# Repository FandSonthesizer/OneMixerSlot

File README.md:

# OneMixerSlot

This is one strip of the modular mixer, it can do voltage controlled panning in the stereo field.

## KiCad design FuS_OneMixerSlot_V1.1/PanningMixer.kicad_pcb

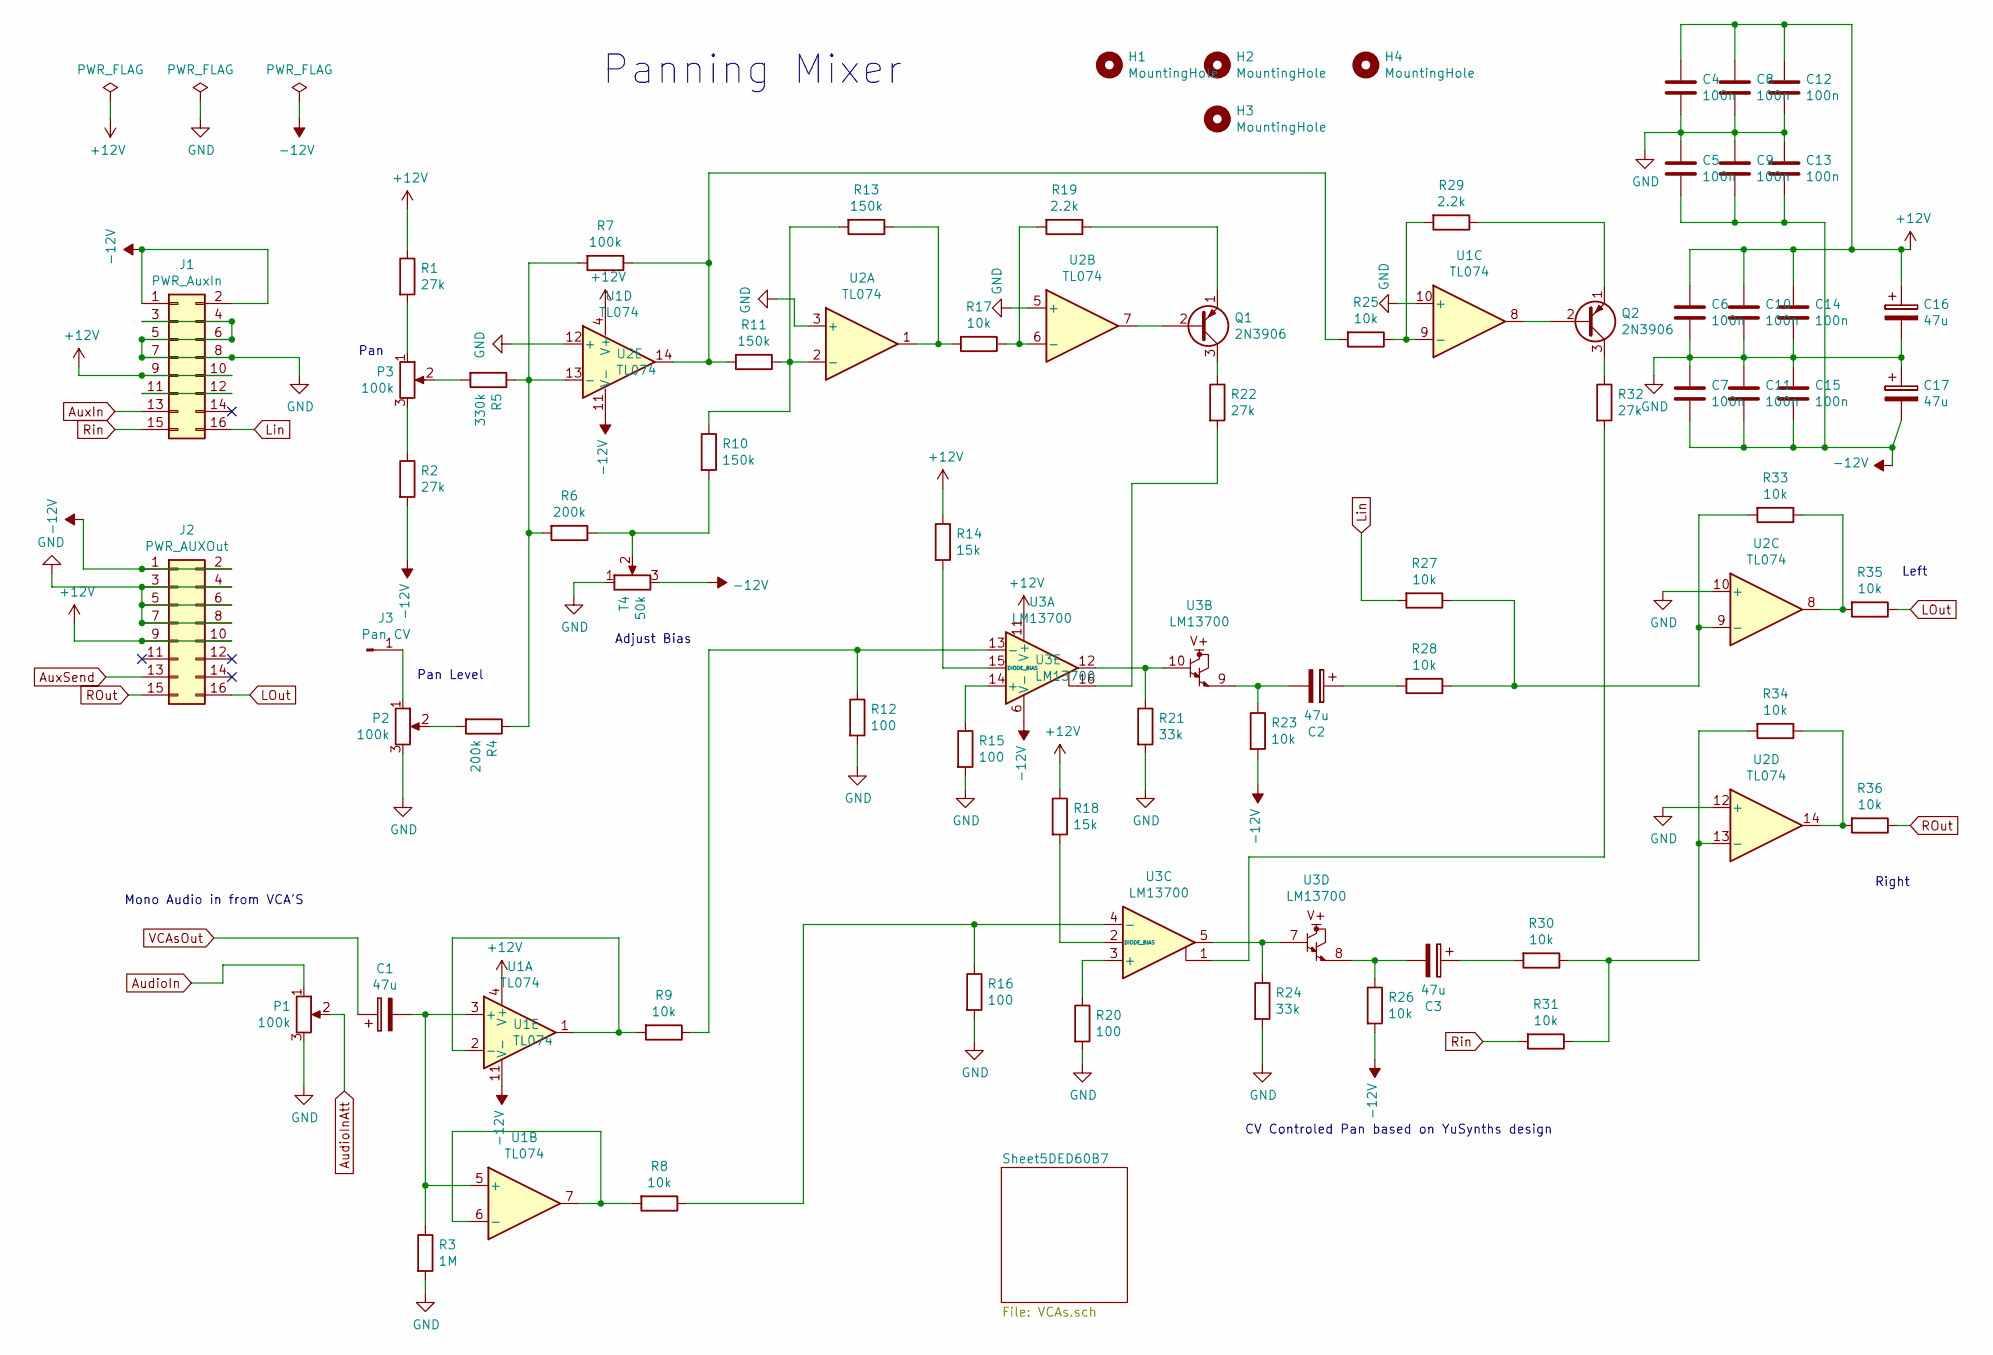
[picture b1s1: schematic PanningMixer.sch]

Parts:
C1, C2, C3, C16, C17: 47u; Elko_D6.3mm_P2.50mm
C4, C5, C6, C7, C8, C9, C10, C11, C12, C13, C14, C15: 100n; Kondensator_Keramik
H1, H2, H3, H4: MountingHole; MountHole
J1: PWR_AuxIn; PinHeader_2x08_P2.54mm_Vertical
J2: PWR_AUXOut; PinHeader_2x08_P2.54mm_Vertical
J3: Pan CV; Stift
P1, P2, P3: 100k; Trimmer_Vertical
Q1, Q2: 2N3906; TO-92L_Wide
R1, R2, R22, R32: 27k; Widerstand_liegend
R3: 1M; Widerstand_liegend
R4, R6: 200k; Widerstand_liegend
R5: 330k; Widerstand_liegend
R7: 100k; Widerstand_liegend
R8, R9, R17, R23, R25, R26, R27, R28, R30, R31, R33, R34, R35, R36: 10k; Widerstand_liegend
R10, R11, R13: 150k; Widerstand_liegend
R12, R15, R16, R20: 100; Widerstand_liegend
R14, R18: 15k; Widerstand_liegend
R19, R29: 2.2k; Widerstand_liegend
R21, R24: 33k; Widerstand_liegend
T4: 50k; Trimmer_Vertical
U1, U2: TL074; DIP-14_W7.62mm_Socket_LongPads
U3: LM13700; DIP-16_W7.62mm_Socket_LongPads

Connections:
+12V: C4.2, C6.2, C8.2, C10.2, C12.2, C14.2, C16.1, J1.9, J1.10, J2.9, J2.10, R1.1, R14.1, R18.1, U1.4 (V+), U2.4 (V+), U3.11 (V+); also elsewhere on the board
-12V: C5.1, C7.1, C9.1, C11.1, C13.1, C15.1, C17.2, J1.1, J1.2, J2.1, J2.2, R2.2, R23.2, R26.2, T4.3, U1.11 (V-), U2.11 (V-), U3.6 (V-); also elsewhere on the board
AudioIn: P1.1; also elsewhere on the board
AudioInAtt: P1.2; also elsewhere on the board
AuxIn: J1.13; also elsewhere on the board
AuxSend: J2.13; also elsewhere on the board
GND: C4.1, C5.2, C6.1, C7.2, C8.1, C9.2, C10.1, C11.2, C12.1, C13.2, C14.1, C15.2, C16.2, C17.1, J1.3, J1.4, J1.5, J1.6, J1.7, J1.8, J2.3, J2.4, J2.5, J2.6, J2.7, J2.8, P1.3, P2.3, R3.2, R12.2, R15.2, R16.2, R20.2, R21.2, R24.2, T4.1, U1.10 (+), U1.12 (+), U2.3 (+), U2.5 (+), U2.10 (+), U2.12 (+); also elsewhere on the board
LOut: J2.16, R35.1
Lin: J1.16, R27.2
unnamed: C1.2, R3.1, U1.3 (+), U1.5 (+)
unnamed: C2.1, R28.2
unnamed: C2.2, R23.1, U3.9
unnamed: C3.1, R30.2
unnamed: C3.2, R26.1, U3.8
unnamed: J1.11, J1.12
unnamed: J3.1, P2.1
unnamed: P2.2, R4.2
unnamed: P3.1, R1.2
unnamed: P3.2, R5.2
unnamed: P3.3, R2.1
unnamed: Q1.1 (E), R19.1
unnamed: Q1.2 (B), U2.7
unnamed: Q1.3 (C), R22.1
unnamed: Q2.1 (E), R29.1
unnamed: Q2.2 (B), U1.8
unnamed: Q2.3 (C), R32.1
unnamed: R4.1, R5.1, R6.2, R7.2, U1.13 (-)
unnamed: R8.2, U1.6 (-), U1.7
unnamed: R9.2, U1.1, U1.2 (-)
unnamed: R10.1, R11.1, R13.2, U2.2 (-)
unnamed: R6.1, R10.2, T4.2
unnamed: R7.1, R11.2, R25.2, U1.14
unnamed: R9.1, R12.1, U3.13 (-)
unnamed: R13.1, R17.2, U2.1
unnamed: R14.2, U3.15 (DIODE_BIAS)
unnamed: R15.1, U3.14 (+)
unnamed: R8.1, R16.1, U3.4 (-)
unnamed: R17.1, R19.2, U2.6 (-)
unnamed: R18.2, U3.2 (DIODE_BIAS)
unnamed: R20.1, U3.3 (+)
unnamed: R21.1, U3.10, U3.12
unnamed: R22.2, U3.16
unnamed: R24.1, U3.5, U3.7
unnamed: R25.1, R29.2, U1.9 (-)
unnamed: R27.1, R28.1, R33.2, U2.9 (-)
unnamed: R30.1, R31.1, R34.2, U2.13 (-)
unnamed: R32.2, U3.1
unnamed: R33.1, R35.2, U2.8
unnamed: R34.1, R36.2, U2.14
ROut: J2.15, R36.1
Rin: J1.15, R31.2
VCAsOut: C1.1; also elsewhere on the board

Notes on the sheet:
Panning Mixer
Pan Level
Pan
Mono Audio in from VCA'S
Adjust Bias
CV Controled Pan based on YuSynths design
Left
Right

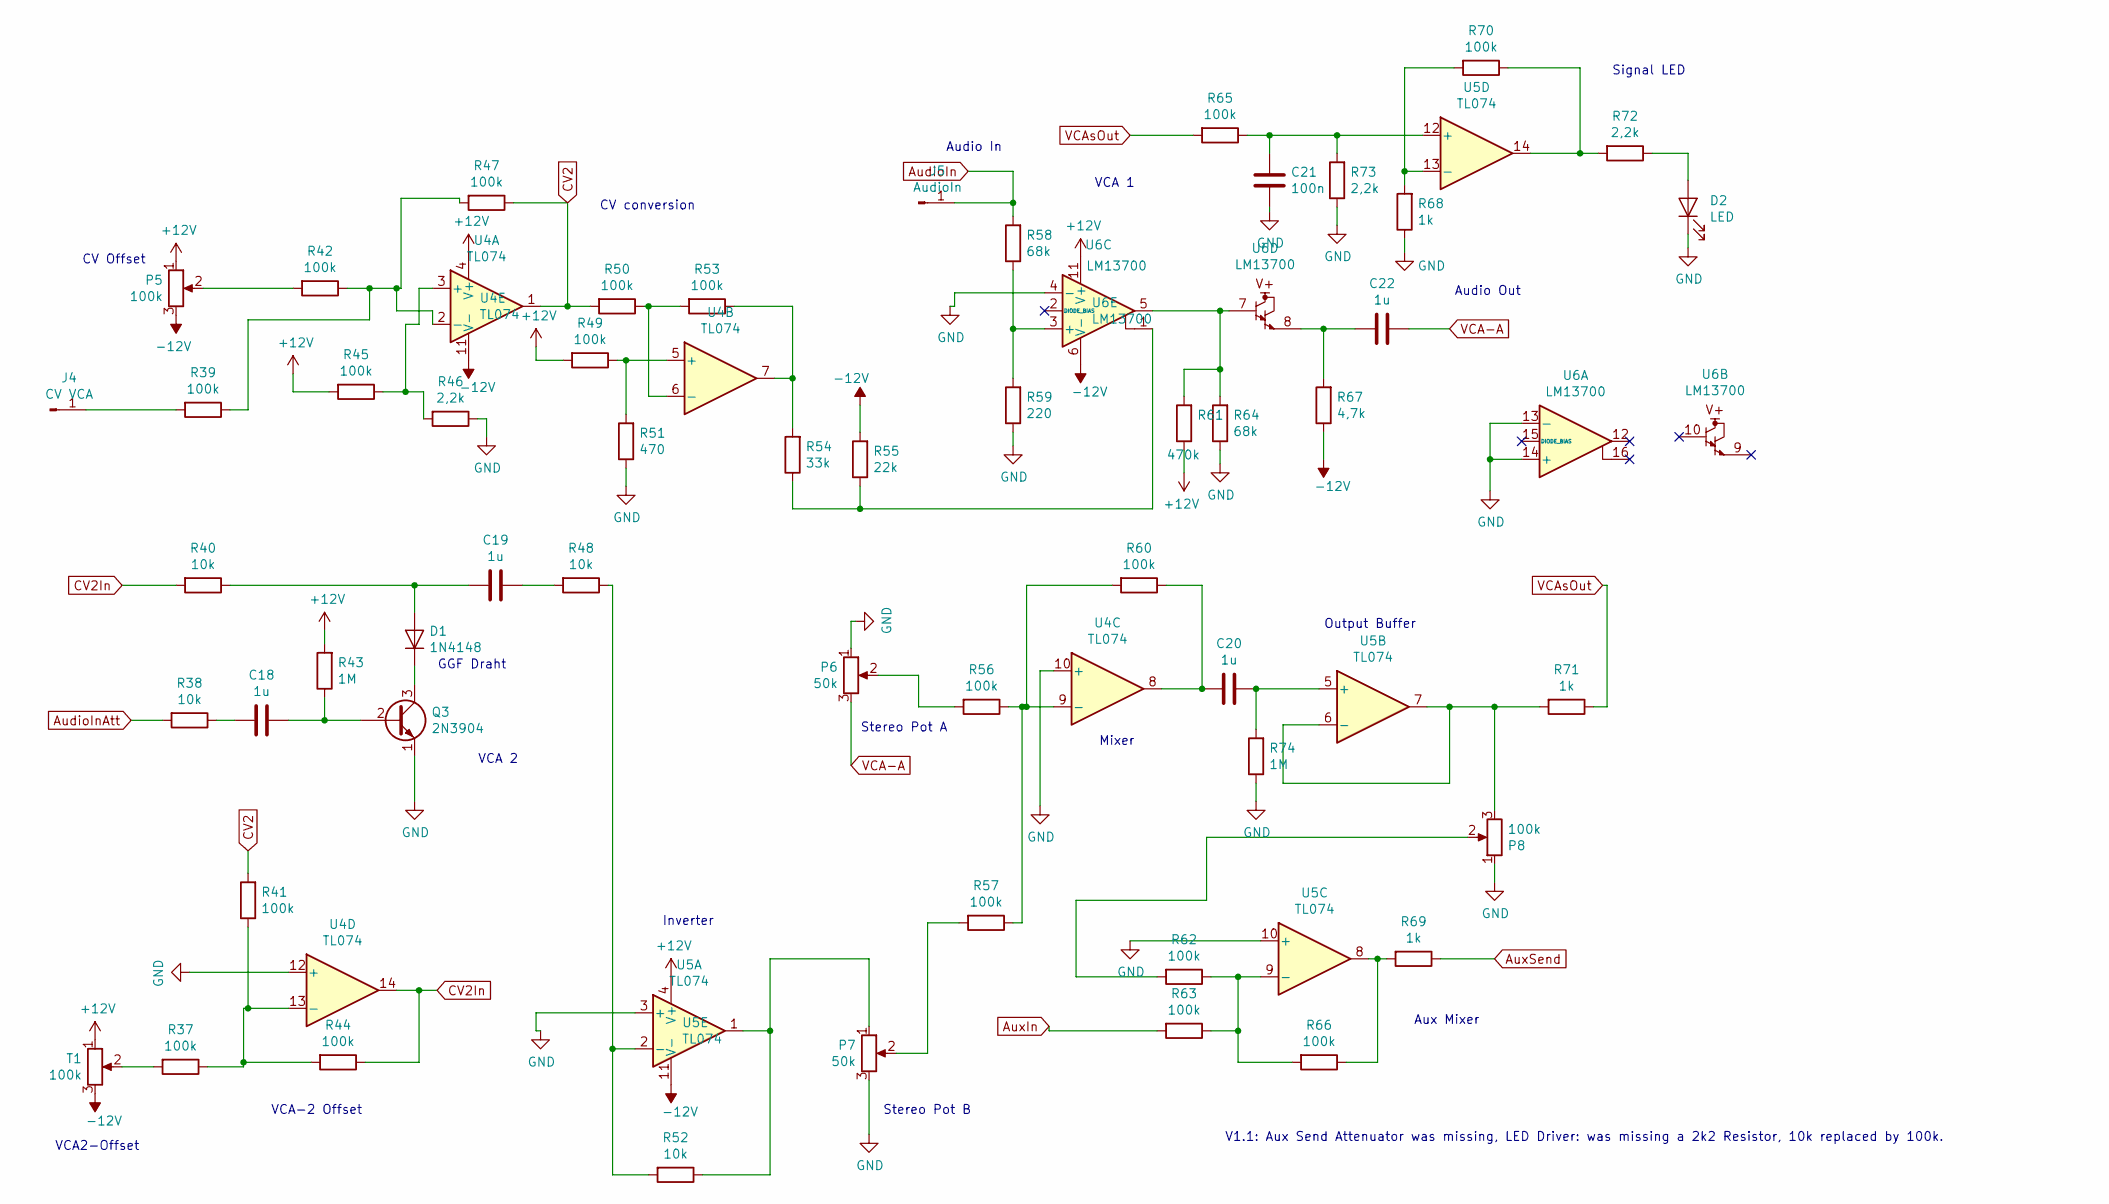
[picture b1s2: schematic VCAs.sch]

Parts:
C18, C19, C20, C22: 1u; Elko_D6.3mm_P2.50mm
C21: 100n; Kondensator_Keramik
D1: 1N4148; Diode_Horizontal
D2: LED; Diode_Horizontal
J4: CV VCA; Stift
J5: AudioIn; Stift
P5, P8: 100k; Trimmer_Vertical
P6, P7: 50k; Trimmer_Vertical
Q3: 2N3904; TO-92L_Wide
R37, R39, R41, R42, R44, R45, R47, R49, R50, R53, R56, R57, R60, R62, R63, R65, R66, R70: 100k; Widerstand_liegend
R38, R40, R48, R52: 10k; Widerstand_liegend
R43, R74: 1M; Widerstand_liegend
R46, R72, R73: 2,2k; Widerstand_liegend
R51: 470; Widerstand_liegend
R54: 33k; Widerstand_liegend
R55: 22k; Widerstand_liegend
R58, R64: 68k; Widerstand_liegend
R59: 220; Widerstand_liegend
R61: 470k; Widerstand_liegend
R67: 4,7k; Widerstand_liegend
R68, R69, R71: 1k; Widerstand_liegend
T1: 100k; Trimmer_Vertical
U4, U5: TL074; DIP-14_W7.62mm_Socket_LongPads
U6: LM13700; DIP-16_W7.62mm_Socket_LongPads

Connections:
+12V: P5.1, R43.2, R45.2, R49.2, R61.1, T1.1, U4.4 (V+), U5.4 (V+), U6.11 (V+); also elsewhere on the board
-12V: P5.3, R55.2, R67.1, T1.3, U4.11 (V-), U5.11 (V-), U6.6 (V-); also elsewhere on the board
AudioIn: J5.1, R58.2; also elsewhere on the board
AudioInAtt: R38.2; also elsewhere on the board
AuxIn: R63.2; also elsewhere on the board
AuxSend: R69.1; also elsewhere on the board
CV2: R41.2, R47.1, R50.2, U4.1
CV2In: R40.2, R44.1, U4.14
GND: C21.2, D2.1 (K), P6.1, P7.3, P8.1, Q3.1 (E), R46.1, R51.1, R59.1, R64.1, R68.1, R73.1, R74.1, U4.10 (+), U4.12 (+), U5.3 (+), U5.10 (+), U6.4 (-), U6.13 (-), U6.14 (+); also elsewhere on the board
unnamed: C18.1, Q3.2 (B), R43.1
unnamed: C18.2, R38.1
unnamed: C19.1, R48.2
unnamed: C19.2, D1.2 (A), R40.1
unnamed: C20.1, R74.2, U5.5 (+)
unnamed: C20.2, R60.1, U4.8
unnamed: C21.1, R65.1, R73.2, U5.12 (+)
unnamed: C22.2, R67.2, U6.8
unnamed: D1.1 (K), Q3.3 (C)
unnamed: D2.2 (A), R72.1
unnamed: J4.1, R39.2
unnamed: P5.2, R42.2
unnamed: P6.2, R56.2
unnamed: P7.1, R52.1, U5.1
unnamed: P7.2, R57.2
unnamed: P8.2, R62.2
unnamed: P8.3, R71.2, U5.6 (-), U5.7
unnamed: R37.1, R41.1, R44.2, U4.13 (-)
unnamed: R37.2, T1.2
unnamed: R39.1, R42.1, R47.2, U4.2 (-)
unnamed: R45.1, R46.2, U4.3 (+)
unnamed: R48.1, R52.2, U5.2 (-)
unnamed: R49.1, R51.2, U4.5 (+)
unnamed: R50.1, R53.2, U4.6 (-)
unnamed: R53.1, R54.2, U4.7
unnamed: R54.1, R55.1, U6.1
unnamed: R56.1, R57.1, R60.2, U4.9 (-)
unnamed: R58.1, R59.2, U6.3 (+)
unnamed: R61.2, R64.2, U6.5, U6.7
unnamed: R62.1, R63.1, R66.2, U5.9 (-)
unnamed: R66.1, R69.2, U5.8
unnamed: R68.2, R70.2, U5.13 (-)
unnamed: R70.1, R72.2, U5.14
VCA-A: C22.1, P6.3
VCAsOut: R65.2, R71.1; also elsewhere on the board

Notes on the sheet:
CV Offset
CV conversion
Audio In
Audio Out
GGF Draht
Mixer
VCA2-Offset
Aux Mixer
Inverter
VCA-2 Offset
Output Buffer
VCA 1
VCA 2
Signal LED
Stereo Pot A
Stereo Pot B
V1.1: Aux Send Attenuator was missing, LED Driver: was missing a 2k2 Resistor, 10k replaced by 100k.

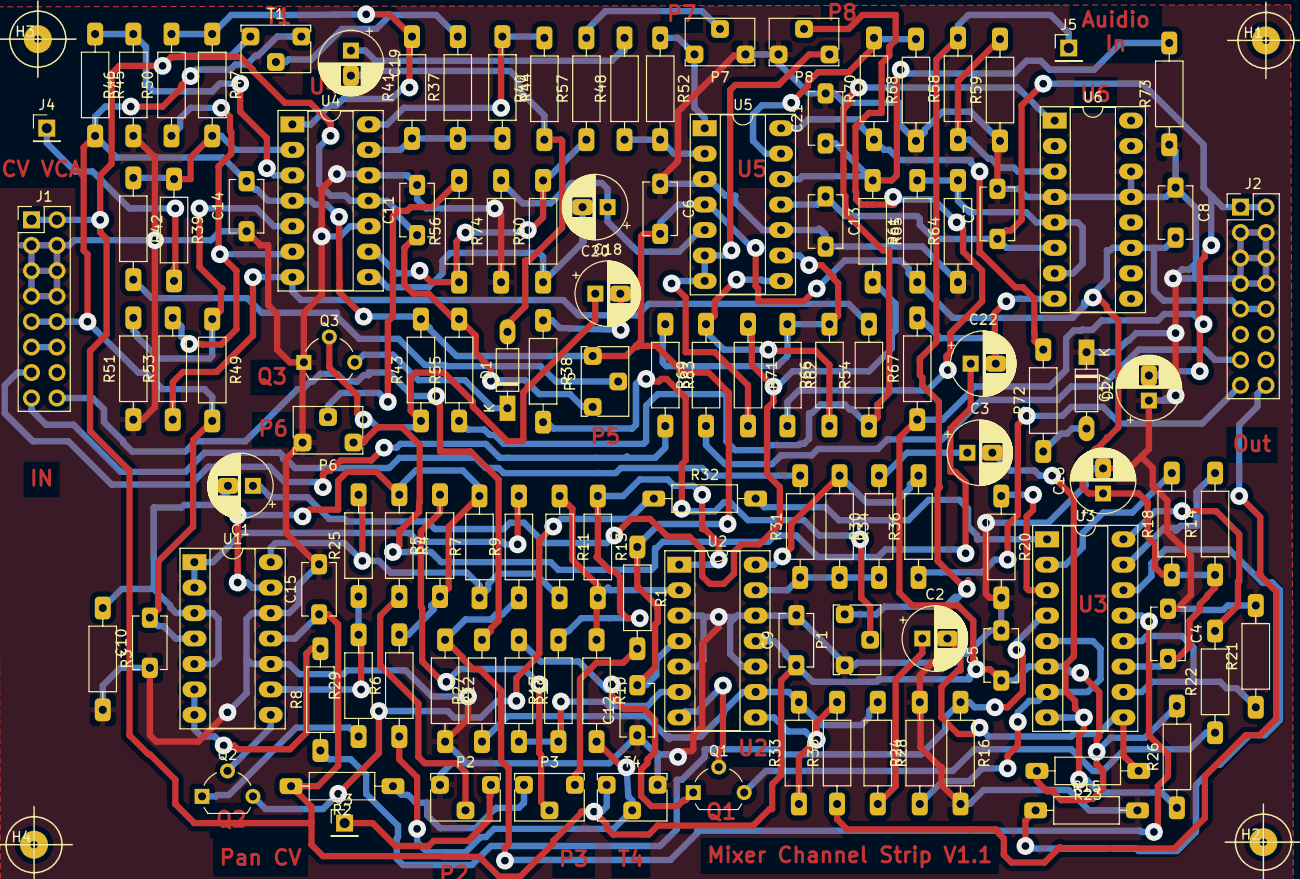
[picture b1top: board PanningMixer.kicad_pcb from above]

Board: 2 copper layers, 125 parts (0 on the bottom side), 88 nets.
